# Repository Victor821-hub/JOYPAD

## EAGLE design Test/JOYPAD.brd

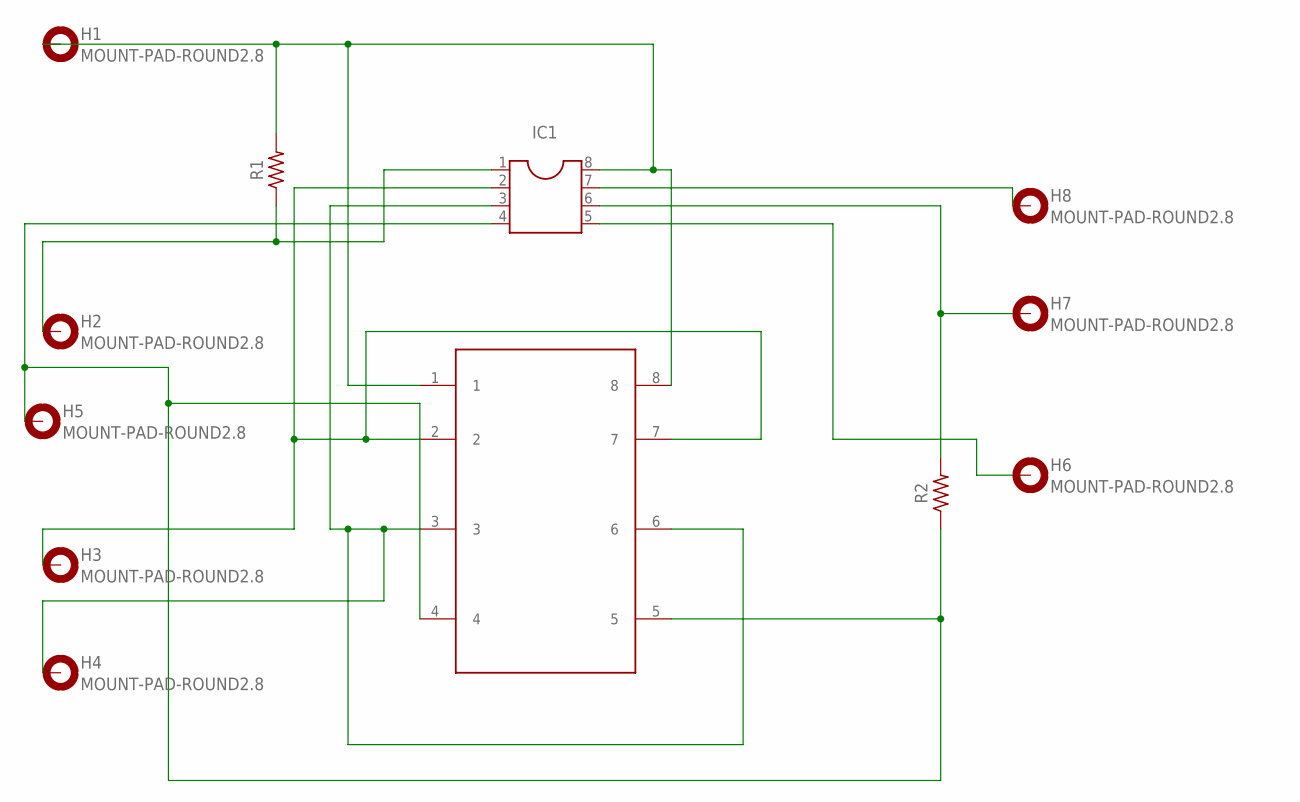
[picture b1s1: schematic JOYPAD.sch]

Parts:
H1, H2, H3, H4, H5, H6, H7, H8: MOUNT-PAD-ROUND2.8; 2,8-PAD
IC1: DIL8; DIL08
R1, R2: R-US_AXIAL-7.2MM-PITCH; RESAD724W46L381D178B
U$1: JOYPAD

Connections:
unnamed: H1.B2,8, IC1.8, R1.2, U$1.1, U$1.8
unnamed: H2.B2,8, IC1.1, R1.1
unnamed: H3.B2,8, IC1.2, U$1.2, U$1.7
unnamed: H4.B2,8, IC1.3, U$1.3, U$1.6
unnamed: H5.B2,8, IC1.4, R2.1, U$1.4, U$1.5
unnamed: H7.B2,8, IC1.6, R2.2
unnamed: H8.B2,8, IC1.7
unnamed: H6.B2,8, IC1.5

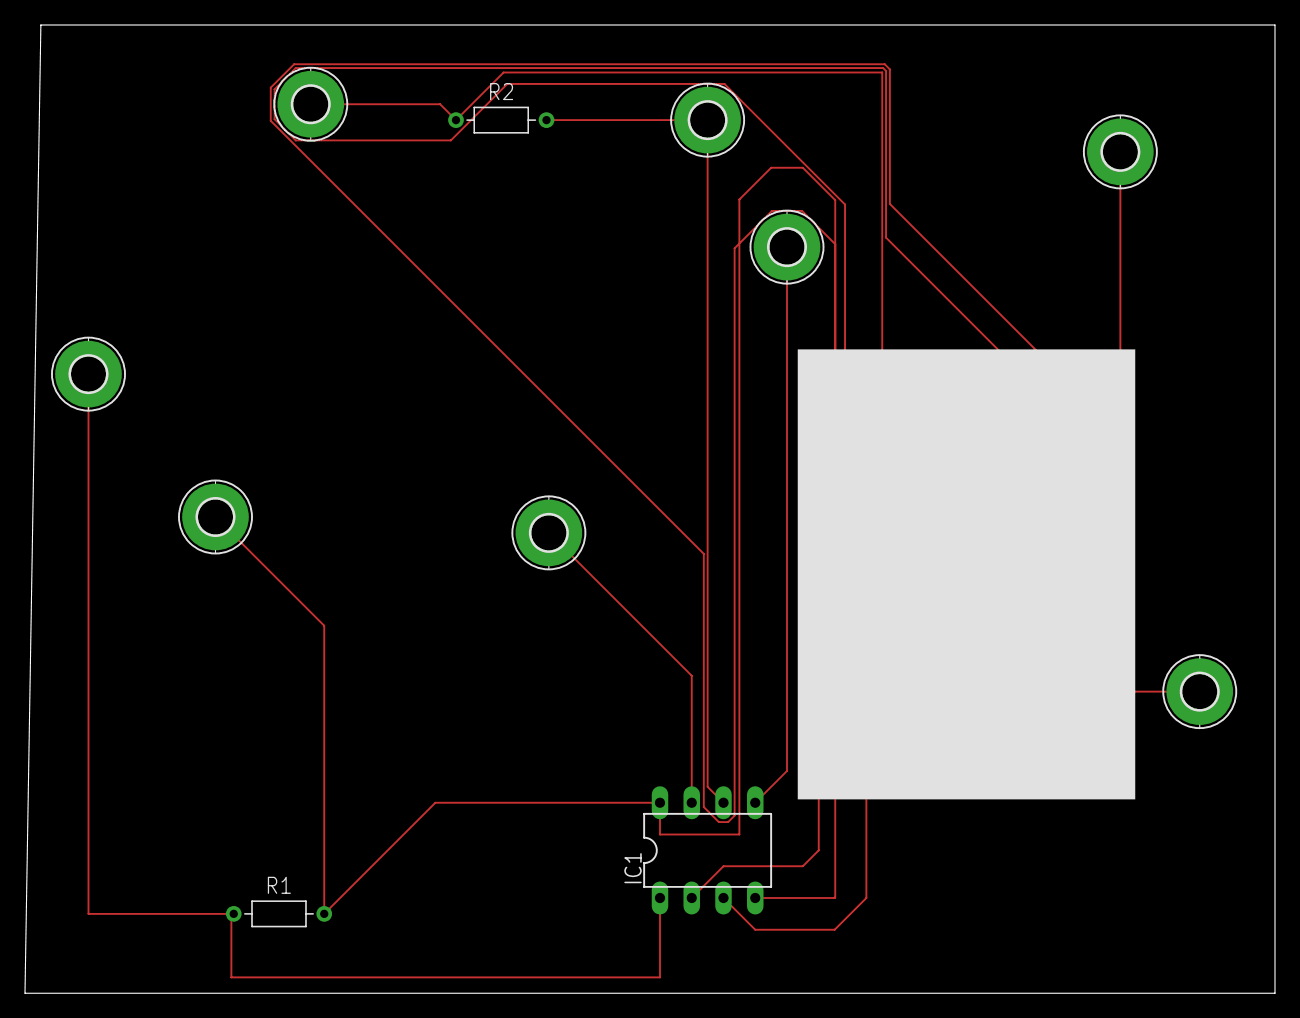
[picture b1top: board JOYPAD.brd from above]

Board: 2 copper layers, 100.0 x 77.5 mm, 12 parts (0 on the bottom side), 8 nets.
